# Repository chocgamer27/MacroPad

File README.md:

# MacroPad
A custom macro pad 
Made by chocolate guy

# challenges
Still trying to figure out fusion and how to model the parts, wiring in KiCad is sometimes a bit messy for me, hopefully I can make more good projects like this!

# Bom

9x  LED_SMD:LED_SK6812MINI_PLCC4_3.5x3.5mm_P1.75mm

9x  Button_Switch_Keyboard:SW_Cherry_MX_1.00u_PCB

9x Blank DSA Keycaps

1x  Seeed Studio XIAO Series Library:XIAO-RP2040-DIP

4x  M3x16 Bolt

4x  M3 Heatset

9x 1N4148 Diodes

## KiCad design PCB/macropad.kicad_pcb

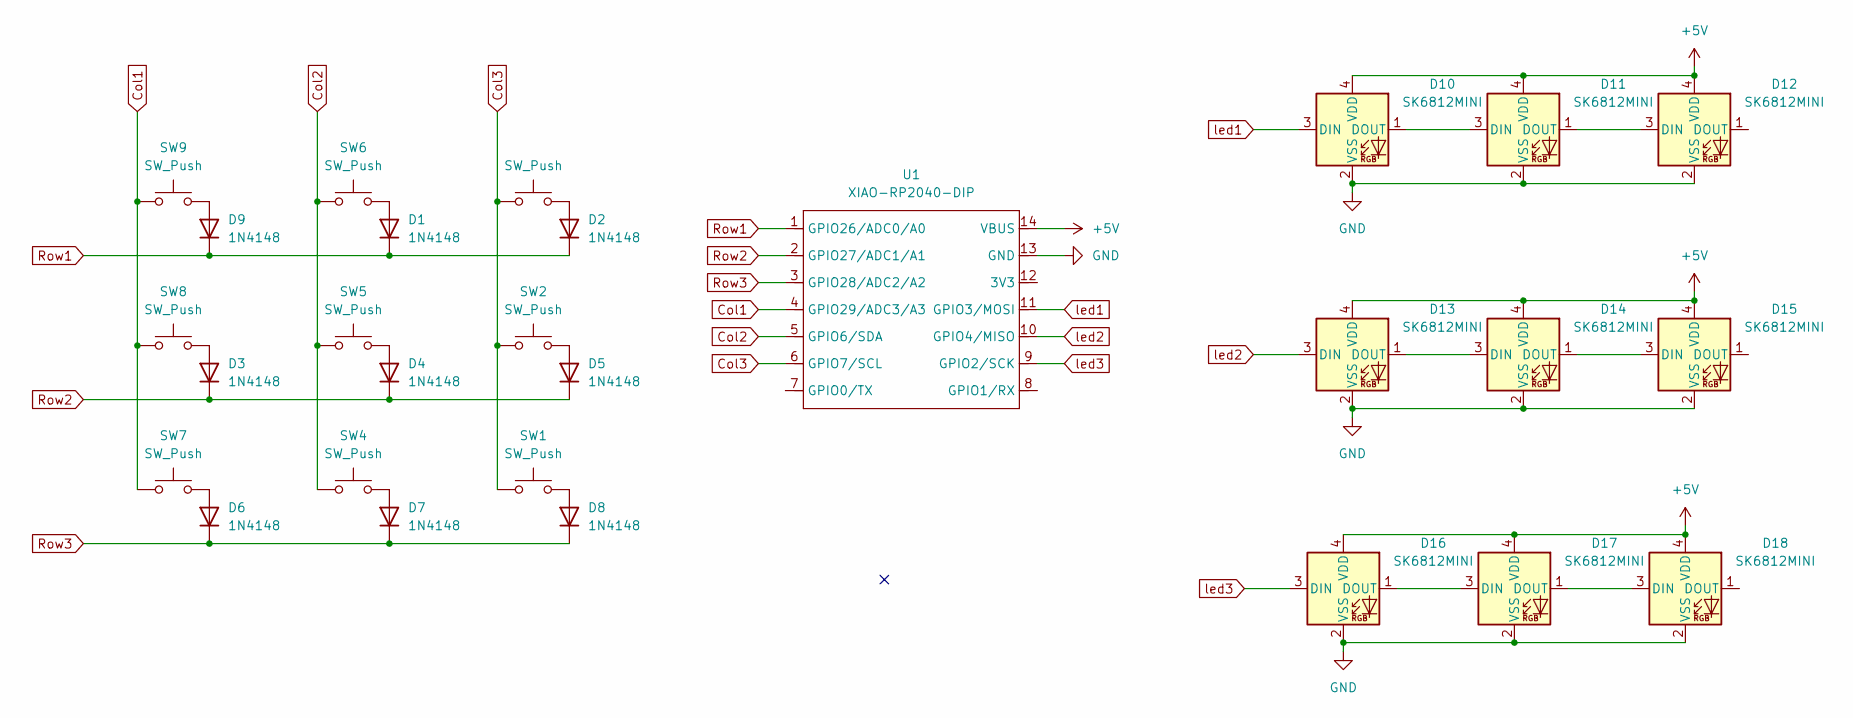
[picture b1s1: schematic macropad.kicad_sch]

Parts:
D1, D2, D3, D4, D5, D6, D7, D8, D9: 1N4148; D_DO-35_SOD27_P7.62mm_Horizontal
D10, D11, D12, D13, D14, D15, D16, D17, D18: SK6812MINI; LED_SK6812MINI_PLCC4_3.5x3.5mm_P1.75mm
SW1, SW2, SW3, SW4, SW5, SW6, SW7, SW8, SW9: SW_Push; SW_Cherry_MX_1.00u_PCB
U1: XIAO-RP2040-DIP

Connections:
+5V: D10.4 (VDD), D11.4 (VDD), D12.4 (VDD), D13.4 (VDD), D14.4 (VDD), D15.4 (VDD), D16.4 (VDD), D17.4 (VDD), D18.4 (VDD), U1.14 (VBUS)
Col1: SW7.1, SW8.1, SW9.1, U1.4 (GPIO29/ADC3/A3)
Col2: SW4.1, SW5.1, SW6.1, U1.5 (GPIO6/SDA)
Col3: SW1.1, SW2.1, SW3.1, U1.6 (GPIO7/SCL)
GND: D10.2 (VSS), D11.2 (VSS), D12.2 (VSS), D13.2 (VSS), D14.2 (VSS), D15.2 (VSS), D16.2 (VSS), D17.2 (VSS), D18.2 (VSS), U1.13 (GND)
unnamed: D1.2 (A), SW6.2
unnamed: D2.2 (A), SW3.2
unnamed: D3.2 (A), SW8.2
unnamed: D4.2 (A), SW5.2
unnamed: D5.2 (A), SW2.2
unnamed: D6.2 (A), SW7.2
unnamed: D7.2 (A), SW4.2
unnamed: D8.2 (A), SW1.2
unnamed: D9.2 (A), SW9.2
unnamed: D10.1 (DOUT), D11.3 (DIN)
unnamed: D11.1 (DOUT), D12.3 (DIN)
unnamed: D13.1 (DOUT), D14.3 (DIN)
unnamed: D14.1 (DOUT), D15.3 (DIN)
unnamed: D16.1 (DOUT), D17.3 (DIN)
unnamed: D17.1 (DOUT), D18.3 (DIN)
Row1: D1.1 (K), D2.1 (K), D9.1 (K), U1.1 (GPIO26/ADC0/A0)
Row2: D3.1 (K), D4.1 (K), D5.1 (K), U1.2 (GPIO27/ADC1/A1)
Row3: D6.1 (K), D7.1 (K), D8.1 (K), U1.3 (GPIO28/ADC2/A2)
led1: D10.3 (DIN), U1.11 (GPIO3/MOSI)
led2: D13.3 (DIN), U1.10 (GPIO4/MISO)
led3: D16.3 (DIN), U1.9 (GPIO2/SCK)

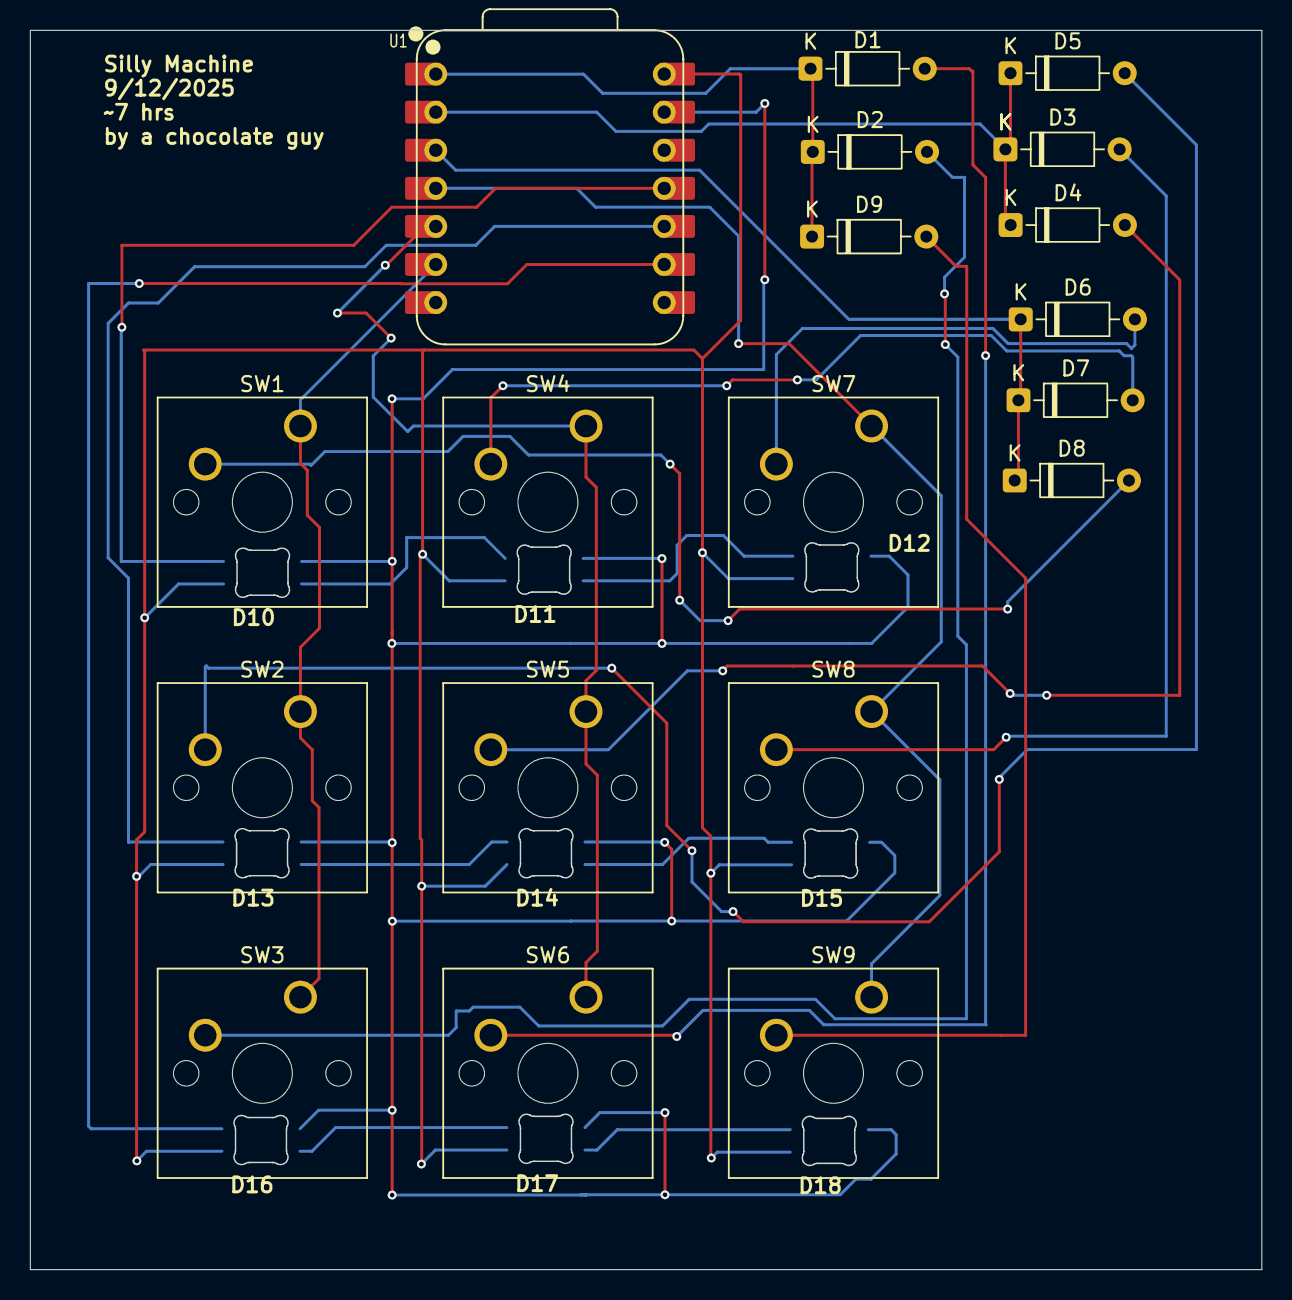
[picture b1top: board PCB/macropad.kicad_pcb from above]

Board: 2 copper layers, 82.2 x 82.7 mm, 28 parts (0 on the bottom side), 26 nets.

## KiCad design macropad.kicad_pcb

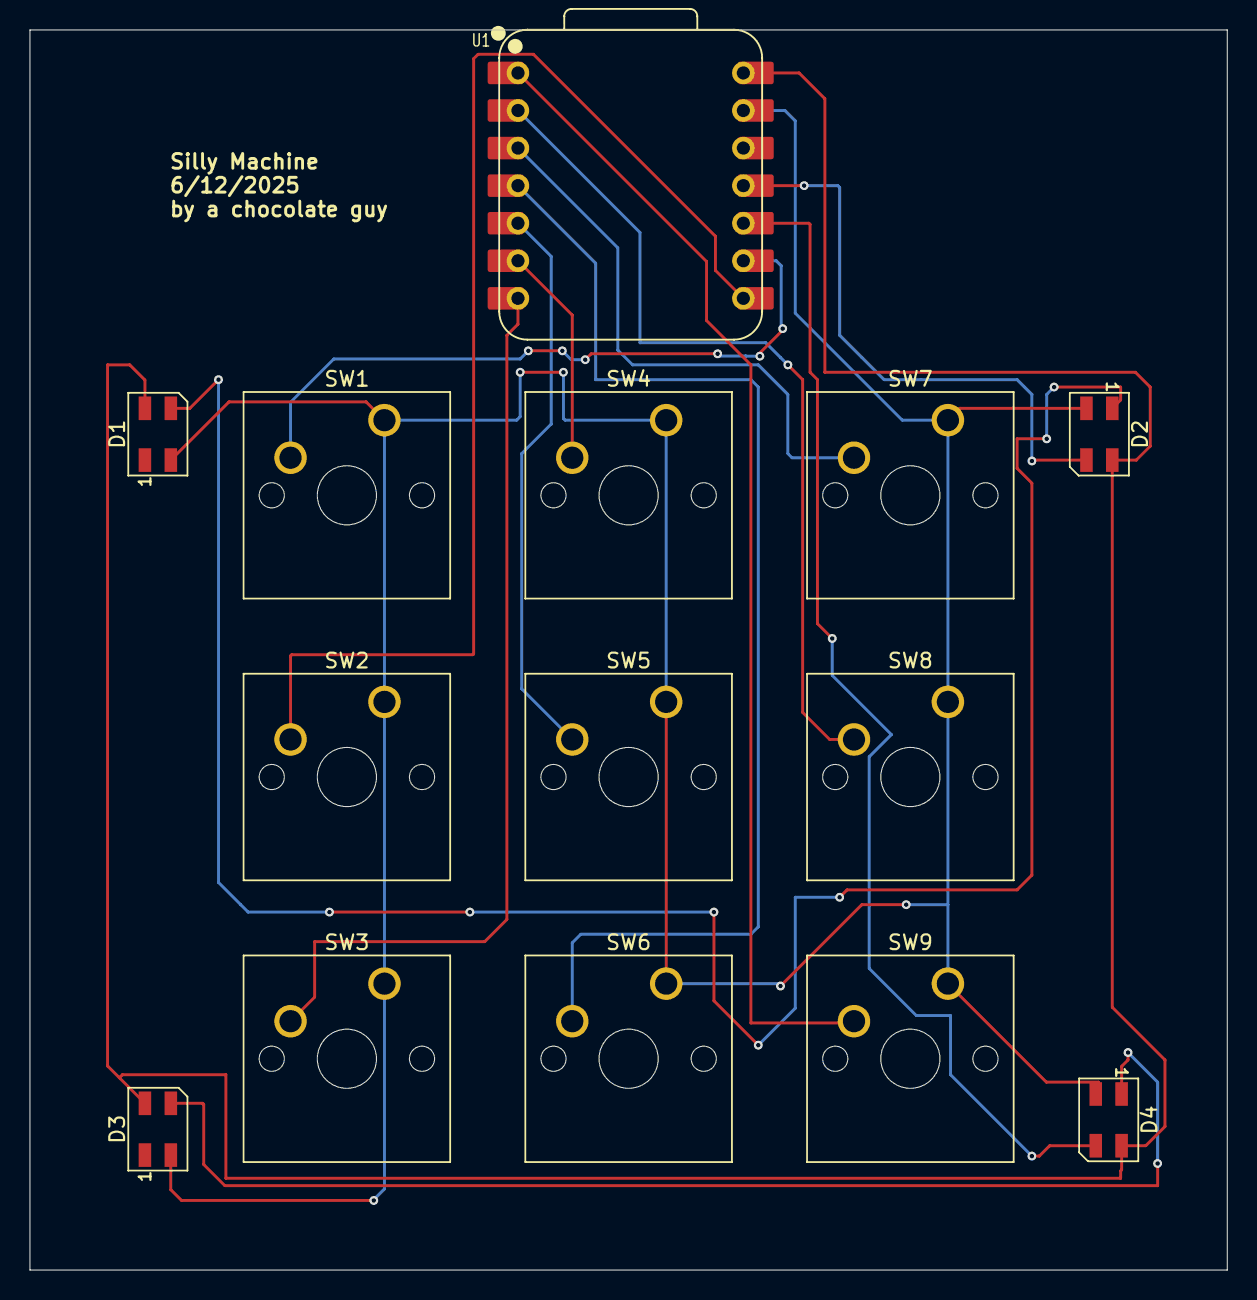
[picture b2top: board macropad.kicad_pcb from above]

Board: 2 copper layers, 81.0 x 83.9 mm, 14 parts (0 on the bottom side), 15 nets.

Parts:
D1, D2, D3, D4: SK6812MINI; LED_SK6812MINI_PLCC4_3.5x3.5mm_P1.75mm
SW1, SW2, SW3, SW4, SW5, SW6, SW7, SW8, SW9: SW_Push; SW_Cherry_MX_1.00u_PCB
U1: XIAO-RP2040-DIP

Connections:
+5V: D1.4 (VDD), D2.4 (VDD), D3.4 (VDD), D4.4 (VDD), U1.14 (VBUS)
GND: D1.2 (VSS), D2.2 (VSS), D3.2 (VSS), D4.2 (VSS), SW1.1, SW2.1, SW3.1, SW4.1, SW5.1, SW6.1, SW7.1, SW8.1, SW9.1, U1.13 (GND)
unnamed: D1.3 (DIN), D2.1 (DOUT)
unnamed: D2.3 (DIN), U1.11 (GPIO3/MOSI)
unnamed: D3.3 (DIN), D4.1 (DOUT)
unnamed: D4.3 (DIN), U1.10 (GPIO4/MISO)
unnamed: SW3.2, U1.7 (GPIO0/TX)
unnamed: SW2.2, U1.8 (GPIO1/RX)
unnamed: SW1.2, U1.9 (GPIO2/SCK)
unnamed: SW5.2, U1.5 (GPIO6/SDA)
unnamed: SW4.2, U1.6 (GPIO7/SCL)
unnamed: SW9.2, U1.1 (GPIO26/ADC0/A0)
unnamed: SW8.2, U1.2 (GPIO27/ADC1/A1)
unnamed: SW7.2, U1.3 (GPIO28/ADC2/A2)
unnamed: SW6.2, U1.4 (GPIO29/ADC3/A3)

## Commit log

2025-12-06 Create a
2025-12-06 Create f
2025-12-07 Create k
